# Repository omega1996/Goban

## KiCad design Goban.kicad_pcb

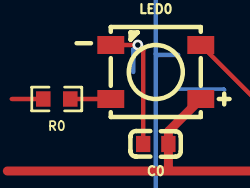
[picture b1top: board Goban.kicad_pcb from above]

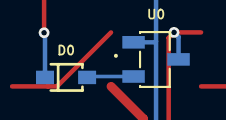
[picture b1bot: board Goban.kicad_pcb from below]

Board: 2 copper layers, 5 parts (2 on the bottom side), 4 nets.

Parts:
C0: C0603B104K500NT; C0603
D0: B5819WS_C488405; SOD-323_L1.8-W1.3-LS2.5-RD
LED0: XL-5050RGBC-WS2812B; LED-SMD_4P-L5.0-W5.0-BL_XL-5050RGBC
R0: RS-03K4700FT; R0603
U0: SLSS49E-3; SOT-23-3_L2.9-W1.6-P1.90-LS2.8-BR-CW

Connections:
GND: C0.1, LED0.3 (GND), U0.2 (GND)
HO0: D0.2 (A), U0.3 (VOUT)
LED0-DIN: LED0.4 (DIN), R0.1
VDD: C0.2, LED0.1 (VDD)

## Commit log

2024-05-04 init
2024-05-07 fixed usb via
2024-05-07 fixed MUX connection
